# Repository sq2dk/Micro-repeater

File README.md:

# Micro-repeater
Two way radio FM micro repeater based on SA-818 modules

This project is by no means complete and finalized. Care must be taken while reproducing, as design might have faults. For radio-amateur use only. You have to have license to experiment with radio transmissions and have to be aware of consequences of your actions!

Repeater can be used to extend usable range of two way portable VHF/UHF radio by placing it in a convenient location between both radios. It consists of receiver (RX) and transmitter (TX) which work at the same time while TX is transmitting everything what is received by RX.
In this project two ready-made TX/RX (SA-818) modules were used. Depending on chosen band of these modules, various band configuration can be achieved. The lowest cost repeater can be done by using 2m / 70cm (cross-band) configuration, since for this you do not need expensive duplexer.

Repository consist of Kicad design files, Arduino code and whatever information might be required.

## Concept:
### -Radio
Small footprint and light weight is achieved by miniature RX/TX modules. Those are based around SDR based chip RDA1847, which is not perfect, but is basically self-contained two-way radio in itself. SA-818 modules consist also microcontroller and power amplifier to achieve about 1W output power. No RF output filtering is made, so at least low-pass filter should be added at the output of TX. RX achieving reasonable sensitivity (better than -120dBm). Communication and set-up of modules is done by serial communication (AT commands). 
### -Microcontroller
Clone of Arduino pro-mini was used. Basically minimal computational power is required, so ATMega328 is more than enough. Small footprint and cost is another benefit. Downside is the programming interface, but almost any USB<->serial TTL interface can be used. Basically it was used, because it was on hand :-).
### -MP3 Player
In some (most?) of the countries, repeaters are required to transmit their call signs aery now and then. This is done by employing small MP3 player module (MP3-TF-16P), which can play MP3 files stored on SD card. On this card various sound files are stored, which also allow transmitting numerical values (such as voltage, temperature etc) by voice. Communication with the module is done by serial protocol.
### -DTMF
DTMF decode module based on MT8870D is added to be able to decode commands sent by user's radio keys. This is fully optional, at the moment requests for voltage, temperature and signal strength are implemented. Others can be coded.
### -Serial communication
As mentioned above, both radio modules and MP3 players are communicating by the serial protocol. All are connected to the same bus, thus additional switches of bus lines (made on transistors) are added, so only one device is able to "talk" with microcontroller at the time. Not perfect, but it works. This has added a lot of complexity to the design, but the principle is easy.
### -Power supply
Two voltages are required - 5V for DTMF module and about 4.3 for MP3 and radio modules. Arduino is also powered by 4.3V, which is fine (you have to use 5V variant). Device can be powered by 5V (from USB) or 7-15V. If you supply 5V, it has to be stabilized. Do not connect both sources at the same time. If you use 5V input jumper pin has to be installed. 5-15V is feed to DC-DC buck converter based on ready module and converted to 4.3V. In case of 7-15V input, 5V is produced by 78L05 linear stabilizer, in case of 5V supply it is feed directly. Reverse-polarity diode is installed, so in case of connection 7-15V short will be made.
### -Others
DS18D20 1-wire temperature sensor can be connected to get temperature readings
2 pins are provided to connect voltage reading. Voltages up to 20V should be fine (voltage divider can be changed in case of other requirements). Calibration of readings is required in software in case of using.

## PCB
PCB is designed to be able to do as single layer at home. Most of the traces are thick, as I was using home-made PCBs for prototyping. In case of homemade PCB recommend to use 2-layer PCB and leave one side with full-copper (ground) layer. Some "bodge" wires are unfortunately required. Complete device has dimensions of approx 10 x 10 x 2 cm. It can definitely be shrunk-down, by re-designing PCB.

## Challenges:
-Power consumption - at the moment, it is not optimized for power consumption. Additional power-save modes are required in software (and in hardware)
-RF interference - modules and their surroundings require additional shielding. On entrance of RX, strong remains of TX transmission is present. Additional shielding of both modules should be made.

Jedrzej Marsz SQ2DK

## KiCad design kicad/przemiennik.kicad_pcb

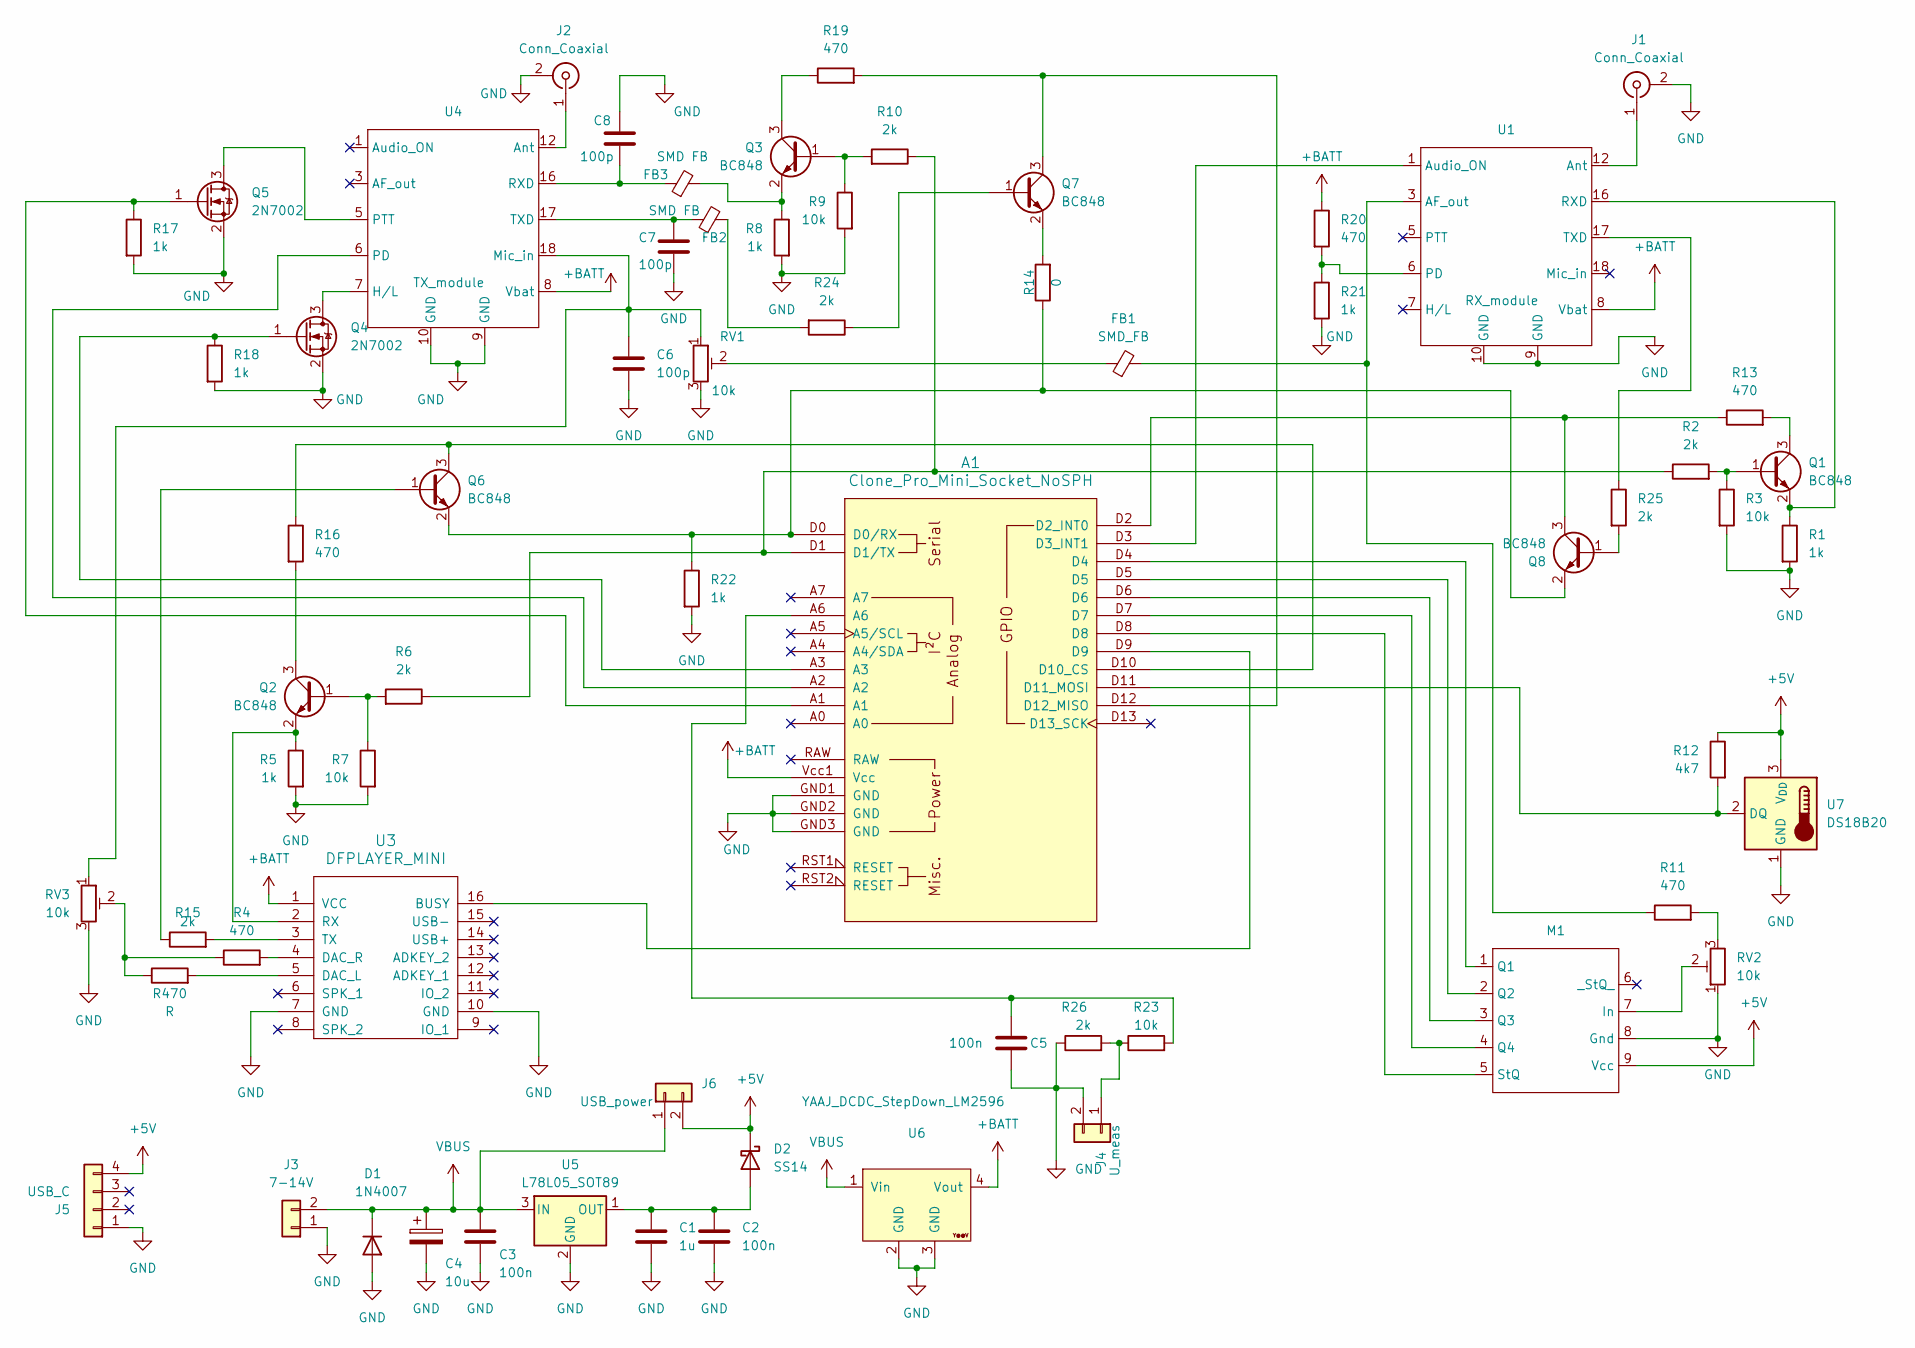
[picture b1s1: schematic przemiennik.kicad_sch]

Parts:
A1: Clone_Pro_Mini_Socket_NoSPH
C1: 1u; C_1206_3216Metric_Pad1.33x1.80mm_HandSolder
C2, C3, C5: 100n; C_1206_3216Metric_Pad1.33x1.80mm_HandSolder
C4: 10u; CP_Elec_6.3x3
C6, C7, C8: 100p; C_1206_3216Metric_Pad1.33x1.80mm_HandSolder
D1: 1N4007; D_SMB_Handsoldering
D2: SS14; D_SMB_Handsoldering
FB1: SMD_FB; L_1206_3216Metric
FB2, FB3: SMD FB; L_1206_3216Metric
J1, J2: Conn_Coaxial; SMA_Samtec_SMA-J-P-X-ST-EM1_EdgeMount
J3: 7-14V; Wago_734-132_1x02_P3.50mm_Vertical
J4: U_meas; PinHeader_1x02_P2.54mm_Vertical
J5: USB_C; PinHeader_1x04_P2.54mm_Vertical
J6: USB_power; PinHeader_1x02_P2.54mm_Vertical
M1: mt8870_module
Q1, Q2, Q3, Q6, Q7, Q8: BC848; SOT-23
Q4, Q5: 2N7002; SOT-23
R1, R5, R8, R17, R18, R21, R22: 1k; R_1206_3216Metric_Pad1.30x1.75mm_HandSolder
R2, R6, R10, R15, R24, R25, R26: 2k; R_1206_3216Metric_Pad1.30x1.75mm_HandSolder
R3, R7, R9, R23: 10k; R_1206_3216Metric_Pad1.30x1.75mm_HandSolder
R4, R11, R13, R16, R19, R20: 470; R_1206_3216Metric_Pad1.30x1.75mm_HandSolder
R12: 4k7; R_1206_3216Metric_Pad1.30x1.75mm_HandSolder
R14: 0; R_1206_3216Metric_Pad1.30x1.75mm_HandSolder
R470: R; R_1206_3216Metric_Pad1.30x1.75mm_HandSolder
RV1, RV2, RV3: 10k; Potentiometer_Bourns_3314S_Horizontal
U1: RX_module; DRA818
U3: DFPLAYER_MINI; DFPlayer_V2
U4: TX_module; DRA818
U5: L78L05_SOT89; SOT-89-3
U6: YAAJ_DCDC_StepDown_LM2596
U7: DS18B20; TO-92

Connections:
+5V: D2.1 (K), J5.4, J6.2, M1.9 (Vcc), R12.1, U7.3 (V_{DD})
+BATT: A1.Vcc1 (Vcc), R20.1, U1.8 (Vbat), U3.1 (VCC), U4.8 (Vbat), U6.4 (Vout)
GND: A1.GND1 (GND), A1.GND2 (GND), A1.GND3 (GND), C1.2, C2.2, C3.2, C4.2, C5.2, C6.2, C7.2, C8.1, D1.2 (A), J1.2 (Ext), J2.2 (Ext), J3.1, J4.2, J5.1, M1.8 (Gnd), Q4.2 (S), Q5.2 (S), R1.2, R3.2, R5.2, R7.2, R8.2, R9.2, R17.2, R18.2, R21.2, R22.2, R26.1, RV1.3, RV2.1, RV3.3, U1.9 (GND), U1.10 (GND), U3.7 (GND), U3.10 (GND), U4.9 (GND), U4.10 (GND), U5.2 (GND), U6.2 (GND), U6.3 (GND), U7.1 (GND)
unnamed: A1.D0 (D0/RX), Q6.2 (E), Q8.2 (E), R14.1, R22.1
unnamed: A1.D1 (D1/TX), R2.1, R6.1, R10.1
unnamed: A1.D2 (D2_INT0), Q8.3 (C), R13.1
unnamed: A1.D3 (D3_INT1), U1.1 (Audio_ON)
unnamed: A1.D10 (D10_CS), Q6.3 (C), R16.1
unnamed: A1.D11 (D11_MOSI), R12.2, U7.2 (DQ)
unnamed: A1.D12 (D12_MISO), Q7.3 (C), R19.2
unnamed: A1.A6, C5.1, R23.2
unnamed: C1.1, C2.1, D2.2 (A), U5.1 (OUT)
unnamed: FB1.1, RV1.2
unnamed: FB2.2, R24.2
unnamed: J1.1 (In), U1.12 (Ant)
unnamed: J2.1 (In), U4.12 (Ant)
unnamed: J4.1, R23.1, R26.2
unnamed: M1.7 (In), RV2.2
unnamed: A1.D4, M1.1 (Q1)
unnamed: A1.D5, M1.2 (Q2)
unnamed: A1.D6, M1.3 (Q3)
unnamed: A1.D7, M1.4 (Q4)
unnamed: A1.D8, M1.5 (StQ)
unnamed: Q1.1 (B), R2.2, R3.1
unnamed: Q1.3 (C), R13.2
unnamed: Q1.2 (E), R1.1, U1.16 (RXD)
unnamed: Q2.1 (B), R6.2, R7.1
unnamed: Q2.3 (C), R16.2
unnamed: Q2.2 (E), R5.1, U3.2 (RX)
unnamed: Q3.1 (B), R9.1, R10.2
unnamed: Q3.3 (C), R19.1
unnamed: FB3.2, Q3.2 (E), R8.1
unnamed: Q4.3 (D), U4.7 (H/L)
unnamed: A1.A3, Q4.1 (G), R18.1
unnamed: Q5.3 (D), U4.5 (PTT)
unnamed: A1.A1, Q5.1 (G), R17.1
unnamed: Q6.1 (B), R15.1
unnamed: Q7.1 (B), R24.1
unnamed: Q7.2 (E), R14.2
unnamed: Q8.1 (B), R25.2
unnamed: R4.1, R470.1, RV3.2
unnamed: R11.2, RV2.3
unnamed: FB1.2, R11.1, U1.3 (AF_out)
unnamed: R20.2, R21.1, U1.6 (PD)
unnamed: R25.1, U1.17 (TXD)
unnamed: A1.D9, U3.16 (BUSY)
unnamed: R470.2, U3.5 (DAC_L)
unnamed: R4.2, U3.4 (DAC_R)
unnamed: R15.2, U3.3 (TX)
unnamed: C6.1, RV1.1, RV3.1, U4.18 (Mic_in)
unnamed: A1.A2, U4.6 (PD)
unnamed: C8.2, FB3.1, U4.16 (RXD)
unnamed: C7.1, FB2.1, U4.17 (TXD)
VBUS: C3.1, C4.1, D1.1 (K), J3.2, J6.1, U5.3 (IN), U6.1 (Vin)

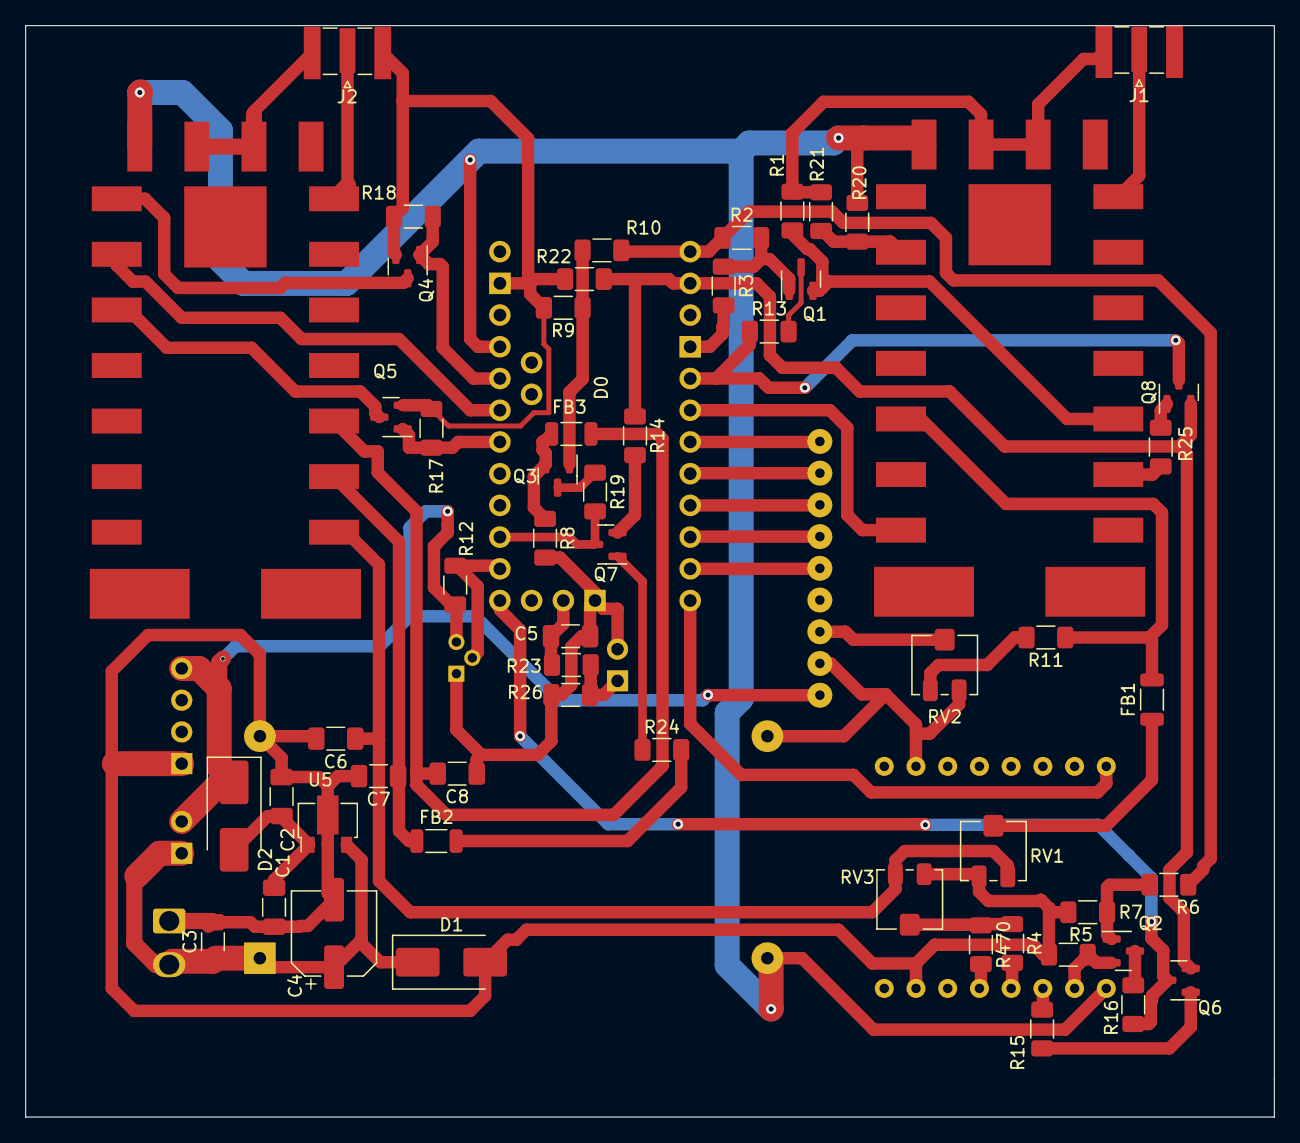
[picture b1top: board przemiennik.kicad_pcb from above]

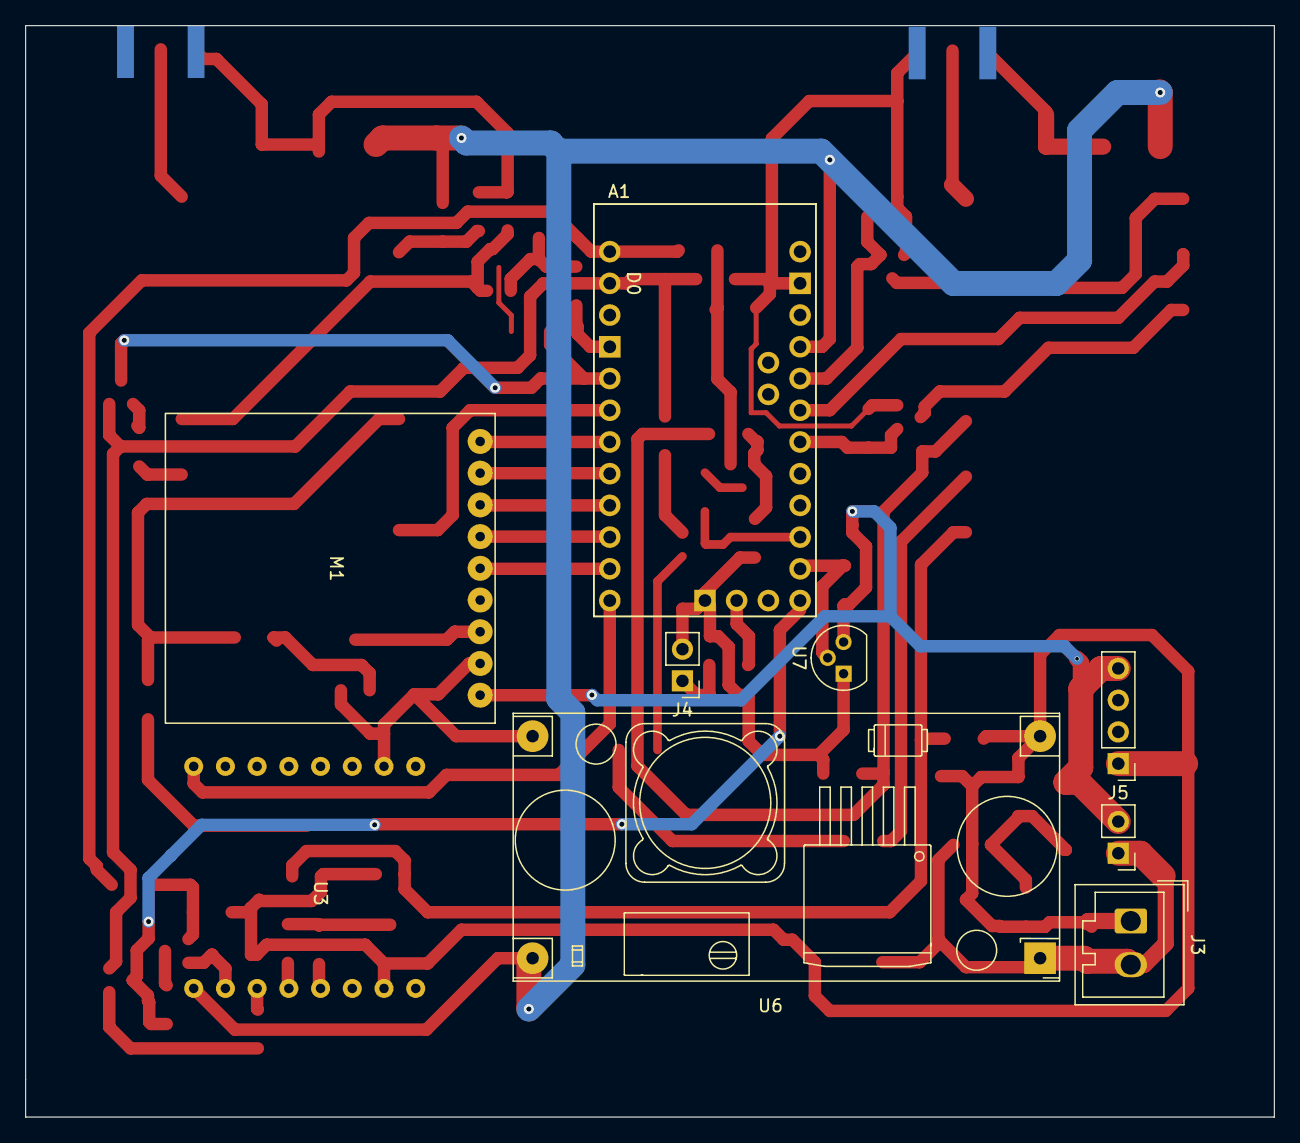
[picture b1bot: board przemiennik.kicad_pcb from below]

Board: 2 copper layers, 100.0 x 87.4 mm, 65 parts (9 on the bottom side), 54 nets.

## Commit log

2024-03-25 Updated files, power save mode added
2024-04-16 Corrected some errors, improved power save
